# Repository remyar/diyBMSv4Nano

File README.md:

# diyBMSv4Nano
Controlleur with arduino nano

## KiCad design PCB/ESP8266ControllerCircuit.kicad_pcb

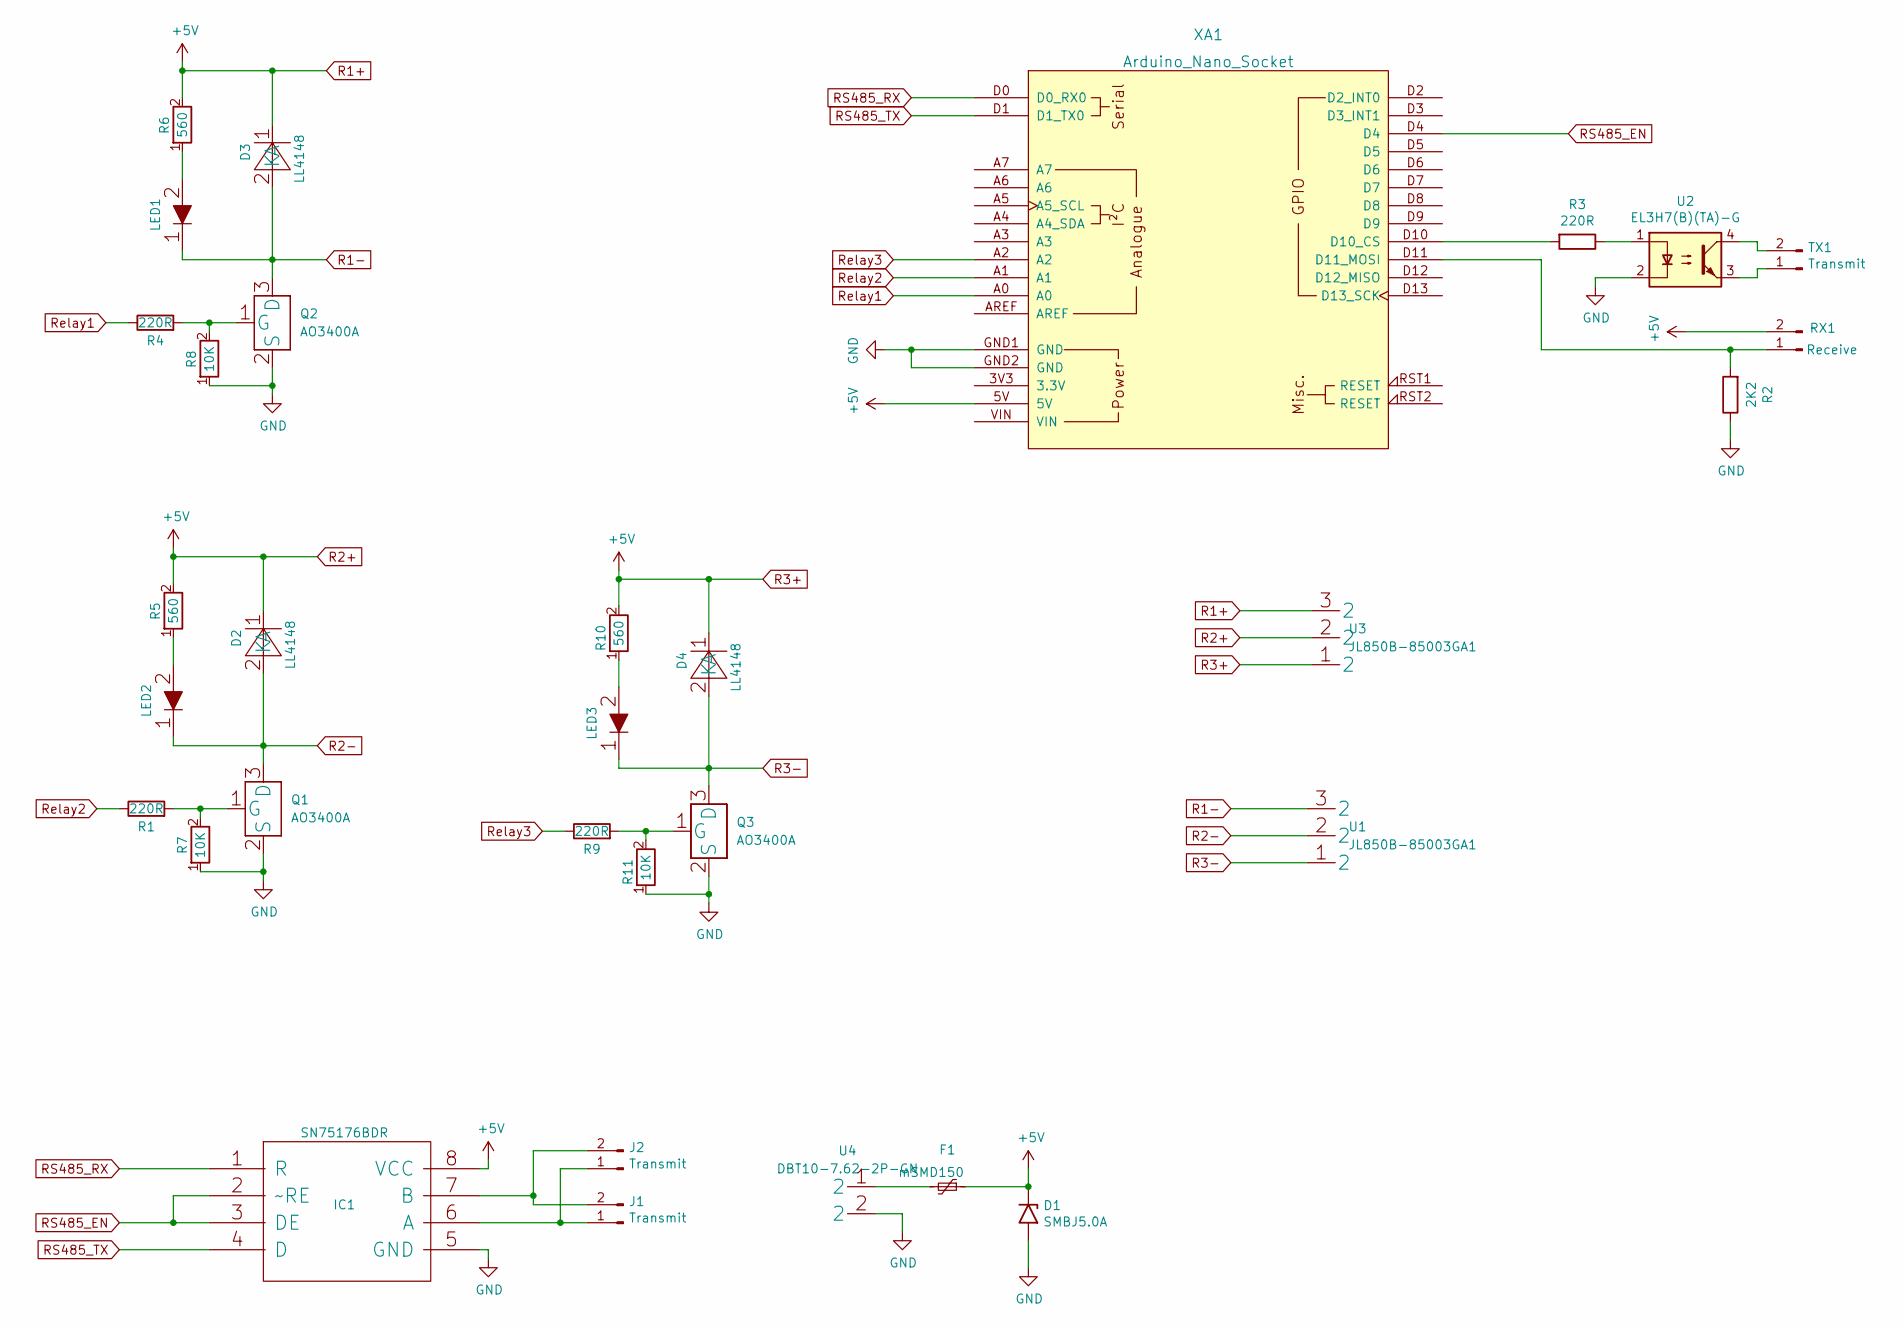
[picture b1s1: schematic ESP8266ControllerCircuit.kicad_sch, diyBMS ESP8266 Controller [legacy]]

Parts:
D1: SMBJ5.0A; diodeSMB; LCSCStockCode C440263
D2, D3, D4: LL4148; LCSC Part Number C9808
F1: mSMD150; fuse; PartNumber mSMD150; LCSCStockCode C70122
IC1: SN75176BDR; Manufacturer_Part_Number SN75176BDR; Mouser Part Number 595-SN75176BDR
J1, J2: Transmit; jst
LED1, LED2, LED3: 19-213_Y2C-CQ2R2L_3T_CY_; 19-213_Y2C-CQ2R2L_3T(CY); Manufacturer_Part_Number 19-213/Y2C-CQ2R2L/3T(CY); LCSC Part Number C72038
Q1, Q2, Q3: AO3400A; LCSC Part Number C344010
R1, R3, R4, R9: 220R; resistor; PartNumber 0805W8F2200T5E; LCSCStockCode C17557
R2: 2K2; resistor; PartNumber 0805W8F2201T5E; LCSCStockCode C17520
R5, R6, R10: 560; resistor; Manufacturer_Part_Number 0805W8F5600T5E; LCSC Part Number C28636
R7, R8, R11: 10K; resistor; Manufacturer_Part_Number 0805W8F1002T5E; LCSC Part Number C17414
RX1: Receive; jst
TX1: Transmit; jst
U1, U3: JL850B-85003GA1; LCSC Part Number C409155
U2: EL3H7(B)(TA)-G; opto; LCSCStockCode C32565
U4: DBT10-7.62-2P-GN; LCSC Part Number C395930
XA1: Arduino_Nano_Socket; arduino_nano

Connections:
GND: D1.2 (A2), IC1.5 (GND), Q1.2 (S), Q2.2 (S), Q3.2 (S), R2.1, R7.1, R8.1, R11.1, U2.2, U4.2, XA1.GND1 (GND), XA1.GND2 (GND)
unnamed: F1.2, U4.1 (2)
unnamed: IC1.6 (A), J1.1, J2.1
unnamed: IC1.7 (B), J1.2, J2.2
unnamed: LED1.2, R6.1
unnamed: LED2.2, R5.1
unnamed: LED3.2, R10.1
unnamed: Q1.1 (G), R1.2, R7.2
unnamed: Q2.1 (G), R4.2, R8.2
unnamed: Q3.1 (G), R9.2, R11.2
unnamed: R2.2, RX1.1, XA1.D11 (D11_MOSI)
unnamed: R3.1, U2.1
unnamed: R3.2, XA1.D10 (D10_CS)
unnamed: TX1.1, U2.3
unnamed: TX1.2, U2.4
R1+: D1.1 (A1), D2.1 (A), D3.1 (A), D4.1 (A), F1.1, IC1.8 (VCC), R5.2, R6.2, R10.2, RX1.2, U3.1 (2), U3.2, U3.3 (2), XA1.5V
R1-: D3.2 (K), LED1.1, Q2.3 (D), U1.3 (2)
R2-: D2.2 (K), LED2.1, Q1.3 (D), U1.2
R3-: D4.2 (K), LED3.1, Q3.3 (D), U1.1 (2)
RS485_EN: IC1.2 (~RE), IC1.3 (DE), XA1.D4
RS485_RX: IC1.1 (R), XA1.D0 (D0_RX0)
RS485_TX: IC1.4 (D), XA1.D1 (D1_TX0)
Relay1: R4.1, XA1.A0
Relay2: R1.1, XA1.A1
Relay3: R9.1, XA1.A2

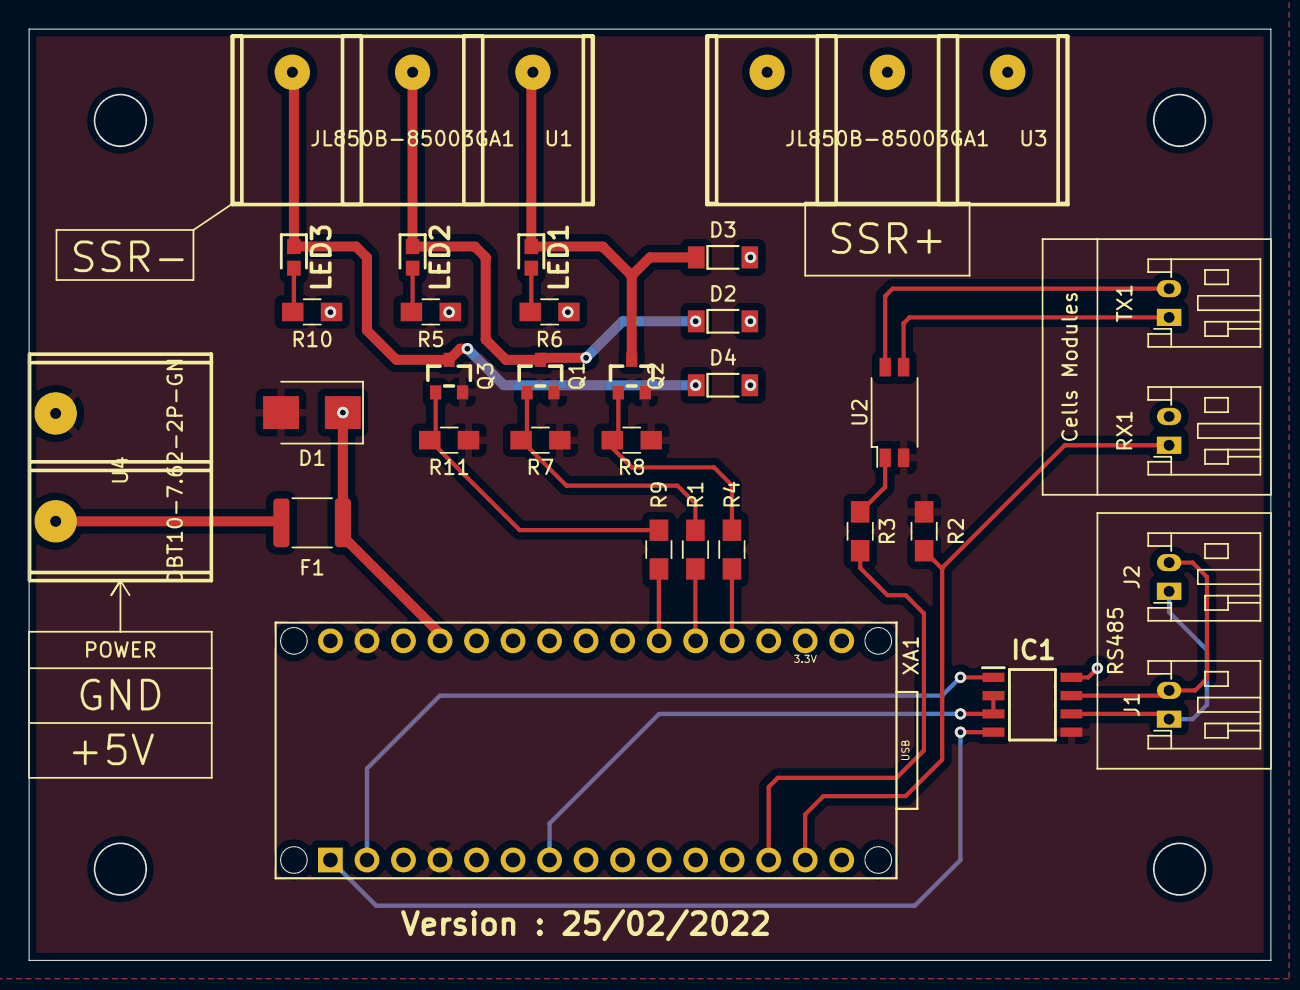
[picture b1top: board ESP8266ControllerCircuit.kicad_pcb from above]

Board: 2 copper layers, 86.3 x 64.7 mm, 32 parts (0 on the bottom side), 25 nets.

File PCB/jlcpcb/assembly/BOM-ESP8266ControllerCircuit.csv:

Comment,Designator,Footprint,LCSC
10K,"R11,R7,R8",resistor,C17414
2K2,R2,resistor,C17520
220R,"R1,R3,R4,R9",resistor,C17557
560,"R10,R5,R6",resistor,C28636
EL3H7(B)(TA)-G,U2,opto,C32565
AO3400A,"Q1,Q2,Q3",AO3400A,C344010
DBT10-7.62-2P-GN,U4,DBT10-7.62-2P-GN,C395930
JL850B-85003GA1,"U1,U3",JL850B-85003GA1,C409155
SMBJ5.0A,D1,diodeSMB,C440263
mSMD150,F1,fuse,C70122
SN75176BDR,IC1,SN75176BDR,C7063
19-213_Y2C-CQ2R2L_3T_CY_,"LED1,LED2,LED3",19-213_Y2C-CQ2R2L_3T(CY),C72038
LL4148,"D2,D3,D4",LL4148,C9808

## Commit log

2022-02-14 add file
2022-02-14 add pcb
2022-02-14 add modbus
2022-02-15 automatic nbcells at start
2022-02-18 ouch
2022-05-02 FGFGFG
2022-05-09 add soft start
